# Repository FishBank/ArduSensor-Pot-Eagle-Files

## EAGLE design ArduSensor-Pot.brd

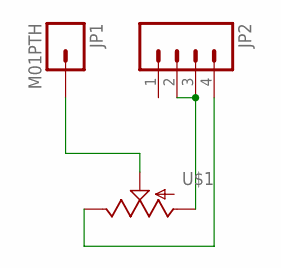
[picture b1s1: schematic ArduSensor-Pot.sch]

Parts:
JP1: M01PTH; 1X01
JP2: M04PTH; 1X04
U$1: POT; ALPS_POT

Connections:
unnamed: JP1.1, U$1.P$2 (S)
unnamed: JP2.2, JP2.3, U$1.P$3 (A)
unnamed: JP2.4, U$1.P$1 (E)

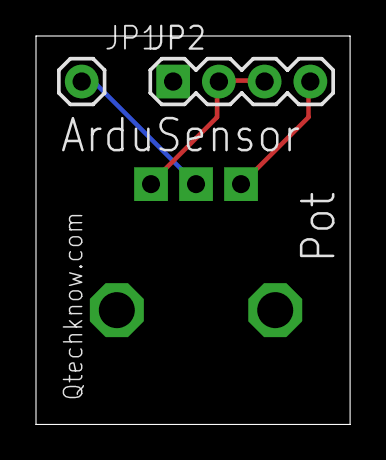
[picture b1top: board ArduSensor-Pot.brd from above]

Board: 2 copper layers, 17.5 x 21.6 mm, 3 parts (0 on the bottom side), 3 nets.

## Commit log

2012-07-13 Schematic

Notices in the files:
parts and their libraries:
SFE Electromechanical: Licensing: CC v3.0 Share-Alike You are welcome to use this library for commercial purposes.
